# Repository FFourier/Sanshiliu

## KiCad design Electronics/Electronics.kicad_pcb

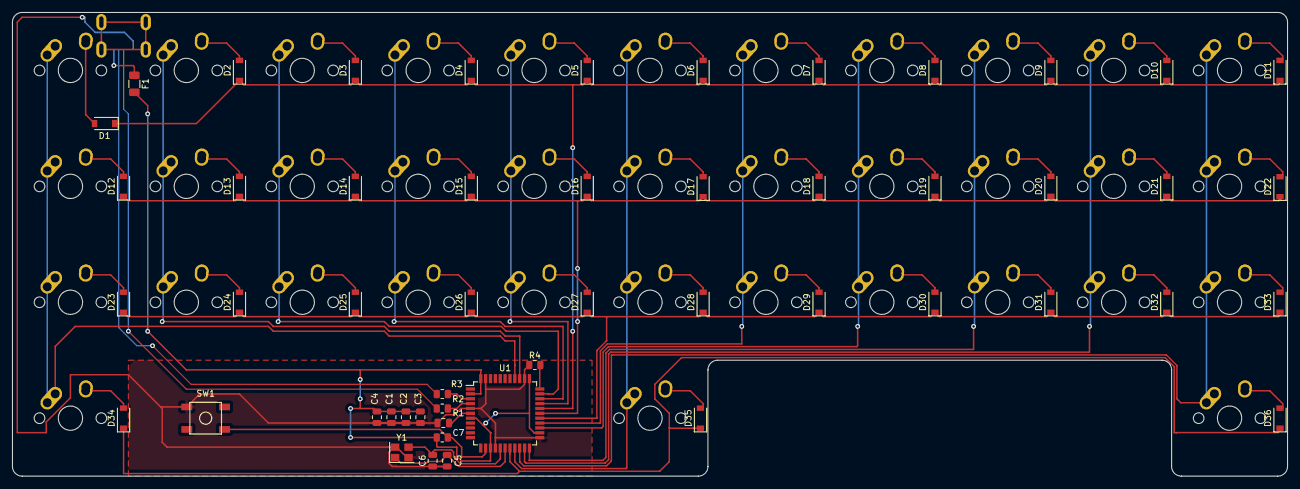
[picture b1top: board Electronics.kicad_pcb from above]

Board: 2 copper layers, 209.6 x 76.2 mm, 88 parts (1 on the bottom side), 63 nets.

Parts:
C1, C2, C3, C4: 0.1uF; C_0805_2012Metric
C5, C6: 22pF; C_0805_2012Metric
C7: 1uF; C_0805_2012Metric
D1, D2, D3, D4, D5, D6, D7, D8, D9, D10, D11, D12, D13, D14, D15, D16, D17, D18, D19, D20, D21, D22, D23, D24, D25, D26, D27, D28, D29, D30, D31, D32, D33, D34, D35, D36: D_Small; D_SOD-123
F1: Polyfuse_Small; Fuse_1206_3216Metric
MX1, MX2, MX3, MX4, MX5, MX6, MX7, MX8, MX9, MX10, MX11, MX12, MX13, MX14, MX15, MX16, MX17, MX18, MX19, MX20, MX21, MX22, MX23, MX24, MX25, MX26, MX27, MX28, MX29, MX30, MX31, MX32, MX33, MX34, MX35, MX36: MX-NoLED; MX-1U-NoLED
R1, R4: 10k; R_0805_2012Metric
R2, R3: 22; R_0805_2012Metric
SW1: SW_Push; SKQG-1155865
U1: ATmega32U4-A; TQFP-44_10x10mm_P0.8mm
USB1: Molex-0548190589
Y1: 16MHz; Crystal_SMD_3225-4Pin_3.2x2.5mm

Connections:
+5V: C1.1, C2.1, C3.1, C4.1, F1.2, R1.1, U1.2 (UVCC), U1.7 (VBUS), U1.14 (VCC), U1.24 (AVCC), U1.34 (VCC), U1.44 (AVCC)
/COL0: MX1.1 (COL), MX12.1 (COL), MX23.1 (COL), MX34.1 (COL), U1.37 (PF6)
/COL1: MX2.1 (COL), MX13.1 (COL), MX24.1 (COL), U1.36 (PF7)
/COL2: MX3.1 (COL), MX14.1 (COL), MX25.1 (COL), U1.32 (PC7)
/COL3: MX4.1 (COL), MX15.1 (COL), MX26.1 (COL), U1.31 (PC6)
/COL4: MX5.1 (COL), MX16.1 (COL), MX27.1 (COL), U1.30 (PB6)
/COL5: MX6.1 (COL), MX17.1 (COL), MX28.1 (COL), MX35.1 (COL), U1.19 (PD1)
/COL6: MX7.1 (COL), MX18.1 (COL), MX29.1 (COL), U1.26 (PD6)
/COL7: MX8.1 (COL), MX19.1 (COL), MX30.1 (COL), U1.25 (PD4)
/COL8: MX9.1 (COL), MX20.1 (COL), MX31.1 (COL), U1.22 (PD5)
/COL9: MX10.1 (COL), MX21.1 (COL), MX32.1 (COL), U1.21 (PD3)
/COL10: MX11.1 (COL), MX22.1 (COL), MX33.1 (COL), MX36.1 (COL), U1.20 (PD2)
/D+: R2.1, USB1.3 (D+)
/D-: R3.1, USB1.4 (D-)
/ROW0: D1.1 (K), D2.1 (K), D3.1 (K), D4.1 (K), D5.1 (K), D6.1 (K), D7.1 (K), D8.1 (K), D9.1 (K), D10.1 (K), D11.1 (K), U1.29 (PB5)
/ROW1: D12.1 (K), D13.1 (K), D14.1 (K), D15.1 (K), D16.1 (K), D17.1 (K), D18.1 (K), D19.1 (K), D20.1 (K), D21.1 (K), D22.1 (K), U1.28 (PB4)
/ROW2: D23.1 (K), D24.1 (K), D25.1 (K), D26.1 (K), D27.1 (K), D28.1 (K), D29.1 (K), D30.1 (K), D31.1 (K), D32.1 (K), D33.1 (K), U1.27 (PD7)
/ROW3: D34.1 (K), D35.1 (K), D36.1 (K), U1.18 (PD0)
GND: C1.2, C2.2, C3.2, C4.2, C5.1, C6.1, C7.2, R4.2, SW1.1, U1.5 (UGND), U1.15 (GND), U1.23 (GND), U1.35 (GND), U1.43 (GND), USB1.1 (GND), Y1.2, Y1.4
unnamed: C5.2, U1.17 (XTAL1), Y1.1
unnamed: C6.2, U1.16 (XTAL2), Y1.3
unnamed: C7.1, U1.6 (UCAP)
unnamed: D1.2 (A), MX1.2 (ROW)
unnamed: D2.2 (A), MX2.2 (ROW)
unnamed: D3.2 (A), MX3.2 (ROW)
unnamed: D4.2 (A), MX4.2 (ROW)
unnamed: D5.2 (A), MX5.2 (ROW)
unnamed: D6.2 (A), MX6.2 (ROW)
unnamed: D7.2 (A), MX7.2 (ROW)
unnamed: D8.2 (A), MX8.2 (ROW)
unnamed: D9.2 (A), MX9.2 (ROW)
unnamed: D10.2 (A), MX10.2 (ROW)
unnamed: D11.2 (A), MX11.2 (ROW)
unnamed: D12.2 (A), MX12.2 (ROW)
unnamed: D13.2 (A), MX13.2 (ROW)
unnamed: D14.2 (A), MX14.2 (ROW)
unnamed: D15.2 (A), MX15.2 (ROW)
unnamed: D16.2 (A), MX16.2 (ROW)
unnamed: D17.2 (A), MX17.2 (ROW)
unnamed: D18.2 (A), MX18.2 (ROW)
unnamed: D19.2 (A), MX19.2 (ROW)
unnamed: D20.2 (A), MX20.2 (ROW)
unnamed: D21.2 (A), MX21.2 (ROW)
unnamed: D22.2 (A), MX22.2 (ROW)
unnamed: D23.2 (A), MX23.2 (ROW)
unnamed: D24.2 (A), MX24.2 (ROW)
unnamed: D25.2 (A), MX25.2 (ROW)
unnamed: D26.2 (A), MX26.2 (ROW)
unnamed: D27.2 (A), MX27.2 (ROW)
unnamed: D28.2 (A), MX28.2 (ROW)
unnamed: D29.2 (A), MX29.2 (ROW)
unnamed: D30.2 (A), MX30.2 (ROW)
unnamed: D31.2 (A), MX31.2 (ROW)
unnamed: D32.2 (A), MX32.2 (ROW)
unnamed: D33.2 (A), MX33.2 (ROW)
unnamed: D34.2 (A), MX34.2 (ROW)
unnamed: D35.2 (A), MX35.2 (ROW)
unnamed: D36.2 (A), MX36.2 (ROW)
unnamed: R1.2, SW1.2, U1.13 (~RESET)
unnamed: R2.2, U1.4 (D+)
unnamed: R3.2, U1.3 (D-)
unnamed: R4.1, U1.33 (~HWB/PE2)
VCC: F1.1, USB1.5 (VBUS)

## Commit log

2022-11-30 Add submodules
2022-11-30 Schematics and layout
2022-12-04 PCB finished with Gerbers
